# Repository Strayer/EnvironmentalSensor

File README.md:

# Environmental Sensor

A WiFi environmental sensor based on Tasmota that reports temperature, air pressure, air quality, humidity and CO2 (ppm).

## Description

It features the following sensors:

- BME 280 / BME 680 - air pressure, air quality (BME 680) and humidity
- MH-Z19B - CO2 (ppm)
- DS18B20 - temperature

The DS18B20 is featured on the PCB because the temperature sensor of the BME 280 / BME 680 is very sensitive - simply holding your finger above it may cause incorrect readings. The DS18B20 is reasonably accurate, cheap and known in the DIY community, so it was a simple addition to get reliable temperature readings.

Either a BME 280 or a BME 680 is supported by the PCB. This was only added because I had a BME 680 lying around, so why not use it - the BME 280 is cheaper and due to the MH-Z19B the air quality reading is pretty obsolete, so in general I recommend installing a BME 280.

The PCB has an internal cutout to avoid transferring heat from the D1 Mini to the temperature-reading components on the other side.

The software intended to be run on the device is [Tasmota](https://github.com/arendst/Tasmota). A preconfigured template will be added later.

## Parts list

- [D1 Mini](https://www.reichelt.de/d1-mini-esp8266-v3-0-d1-mini-p253978.html?search=wemos+d1+mini)
- [BME 280 breakout board](https://amzn.to/2UZ1Zrr)
- [DS18B20](https://www.reichelt.de/digital-thermometer-1-wire--0-5-c-to-92-ds-18b20-p58169.html?&nbc=1)
- [MH-Z19B](https://www.reichelt.de/infrarot-co2-sensor-mh-z19b-co2-mh-z19b-p266033.html)

## Attributions

[MH-Z19B footprint](https://github.com/klein0r/pcb-footprint-collection-kicad/blob/master/MH-Z19B.kicad_mod) (MIT) by [Matthias Kleine (klein0r)](https://github.com/klein0r)

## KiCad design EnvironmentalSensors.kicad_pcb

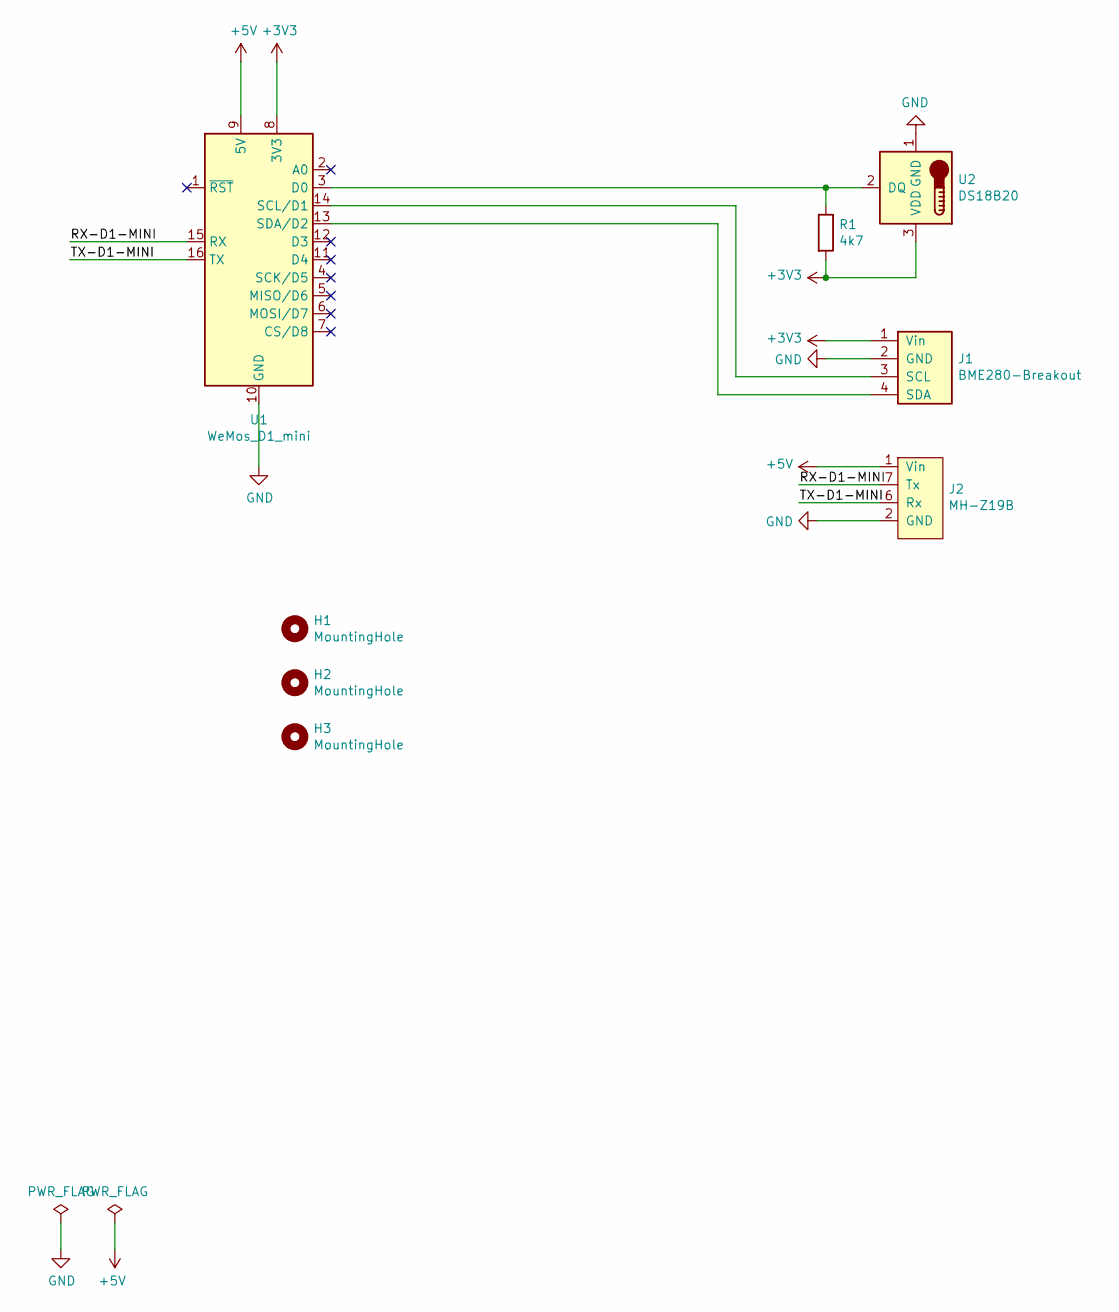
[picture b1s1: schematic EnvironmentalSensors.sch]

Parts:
H1, H2, H3: MountingHole; MountingHole_2.2mm_M2_Pad_Via
J1: BME280-Breakout; BME280_BME680
J2: MH-Z19B
R1: 4k7; R_Axial_DIN0207_L6.3mm_D2.5mm_P10.16mm_Horizontal
U1: WeMos_D1_mini; WEMOS_D1_mini_light
U2: DS18B20; TO-92_Inline

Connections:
+3V3: J1.1 (Vin), R1.2, U1.8 (3V3), U2.3 (VDD)
+5V: J2.1 (Vin), U1.9 (5V)
/RX-D1-MINI: J2.7 (Tx), U1.15 (RX)
/TX-D1-MINI: J2.6 (Rx), U1.16 (TX)
GND: J1.2 (GND), J2.2 (GND), U1.10 (GND), U2.1 (GND)
unnamed: J1.3 (SCL), U1.14 (SCL/D1)
unnamed: J1.4 (SDA), U1.13 (SDA/D2)
unnamed: R1.1, U1.3 (D0), U2.2 (DQ)

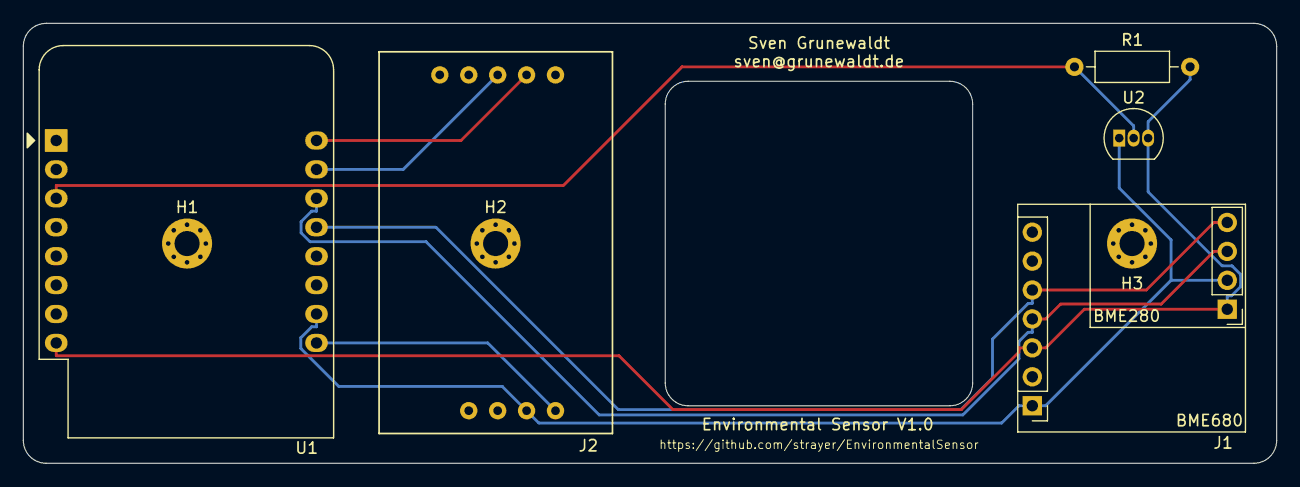
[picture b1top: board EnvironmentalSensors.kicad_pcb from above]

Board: 2 copper layers, 110.1 x 38.6 mm, 8 parts (0 on the bottom side), 8 nets.

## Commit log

2020-08-29 Add LICENSE and mention MH-Z19B footprint origin
2020-11-25 Add description in README.md
